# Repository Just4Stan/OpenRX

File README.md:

# OpenRX

Open-source ExpressLRS receiver family — four active boards:

- `OpenRX-Lite`: compact 2.4 GHz SX1281 receiver with ceramic antenna
- `OpenRX-Lite-UFL`: same as Lite with U.FL antenna connector
- `OpenRX-Mono`: single-LR1121 multi-band receiver with 1x U.FL
- `OpenRX-Gemini`: dual-LR1121 Gemini/Xrossband receiver with 2x U.FL

| Model | Band | RF | Front-End | Antenna | ELRS Target |
|-------|------|-----|-----------|---------|-------------|
| **Lite** | 2.4 GHz | SX1281 | 2450FM07D0034 BPF | Ceramic | `Unified_ESP32C3_2400_RX` |
| **Lite UFL** | 2.4 GHz | SX1281 | 2450FM07D0034 BPF | U.FL | `Unified_ESP32C3_2400_RX` |
| **Mono** | Multi-band | LR1121 | RFX2401C + SKY13414 + Johanson IPD | 1x U.FL | `Unified_ESP32C3_LR1121_RX` |
| **Gemini** | Xrossband | 2x LR1121 | 2x (RFX2401C + SKY13414 + Johanson IPD) | 2x U.FL | `Unified_ESP32C3_LR1121_RX` |

Mono and Gemini use the same firmware binary — `radio_nss_2` in hardware.json activates dual-radio mode.

## Active Schematics

- `OpenRX-Lite/esp32c3_sx1281_lite.kicad_sch`
- `OpenRX-Lite-UFL/esp32c3_sx1281_lite.kicad_sch`
- `OpenRX-Mono/esp32c3_lr1121_mono.kicad_sch`
- `OpenRX-Gemini/esp32c3_lr1121_gemini.kicad_sch`

## Documentation

- `OpenRX-Lite/DESIGN.md`
- `OpenRX-Lite-UFL/DESIGN.md`
- `OpenRX-Mono/DESIGN.md`
- `OpenRX-Gemini/DESIGN.md`

## Flashing

All boards expose `5V`, `GND`, `RX`, `TX` pads and a `BOOT` pad (GPIO9 to GND) for initial UART flashing. Mono and Gemini also have a tactile button on GPIO9. After first flash, use Wi-Fi OTA or Betaflight passthrough.

## ELRS Firmware Targets

Hardware JSON files are in `/shared/elrs-targets/`:

- `OpenRX Lite 2400.json`
- `OpenRX Mono LR1121.json`
- `OpenRX Gemini LR1121.json`
- `targets_entries.json`

## KiCad Libraries

All projects use KiCad 9 with project-local libraries only — no global library dependencies.

`shared/libs/` contains:

| Library | Contents |
|---------|----------|
| `OpenRX-Shared.kicad_sym` | Symbols: ESP32-C3, LR1121, SX1281, RFX2401C, SKY13414, TLV75533, Johanson IPD, 2450FM07D0034, antennas, LED, connectors |
| `OpenRX-Shared.pretty` | Footprints: QFN-14/16/24/32, X2SON, antenna, filter, LED, switch, solder pads |
| `OpenRX-Shared.3dshapes` | 3D models (.step + .wrl) |

All symbols include an `LCSC Part` property for JLCPCB BOM export.

## Datasheets

Shared local cache in `datasheets/common/`. All active IC/RF datasheets are present locally.

## Sourcing

Current low-stock / JLCPCB Global Sourcing candidates:

- `C255353` SKY13414-485LF
- `C19842466` 0900PC16J0042001E (consign from DigiKey)
- `C7498014` LR1121IMLTRT
- `C2151551` SX1281IMLTRT (for 1000 pcs Lite build)
- `C2651081` 2450FM07D0034

## License

**CERN Open Hardware Licence Version 2 - Strongly Reciprocal** ([CERN-OHL-S-2.0](https://ohwr.org/cern_ohl_s_v2.txt)). See [LICENSE](LICENSE).

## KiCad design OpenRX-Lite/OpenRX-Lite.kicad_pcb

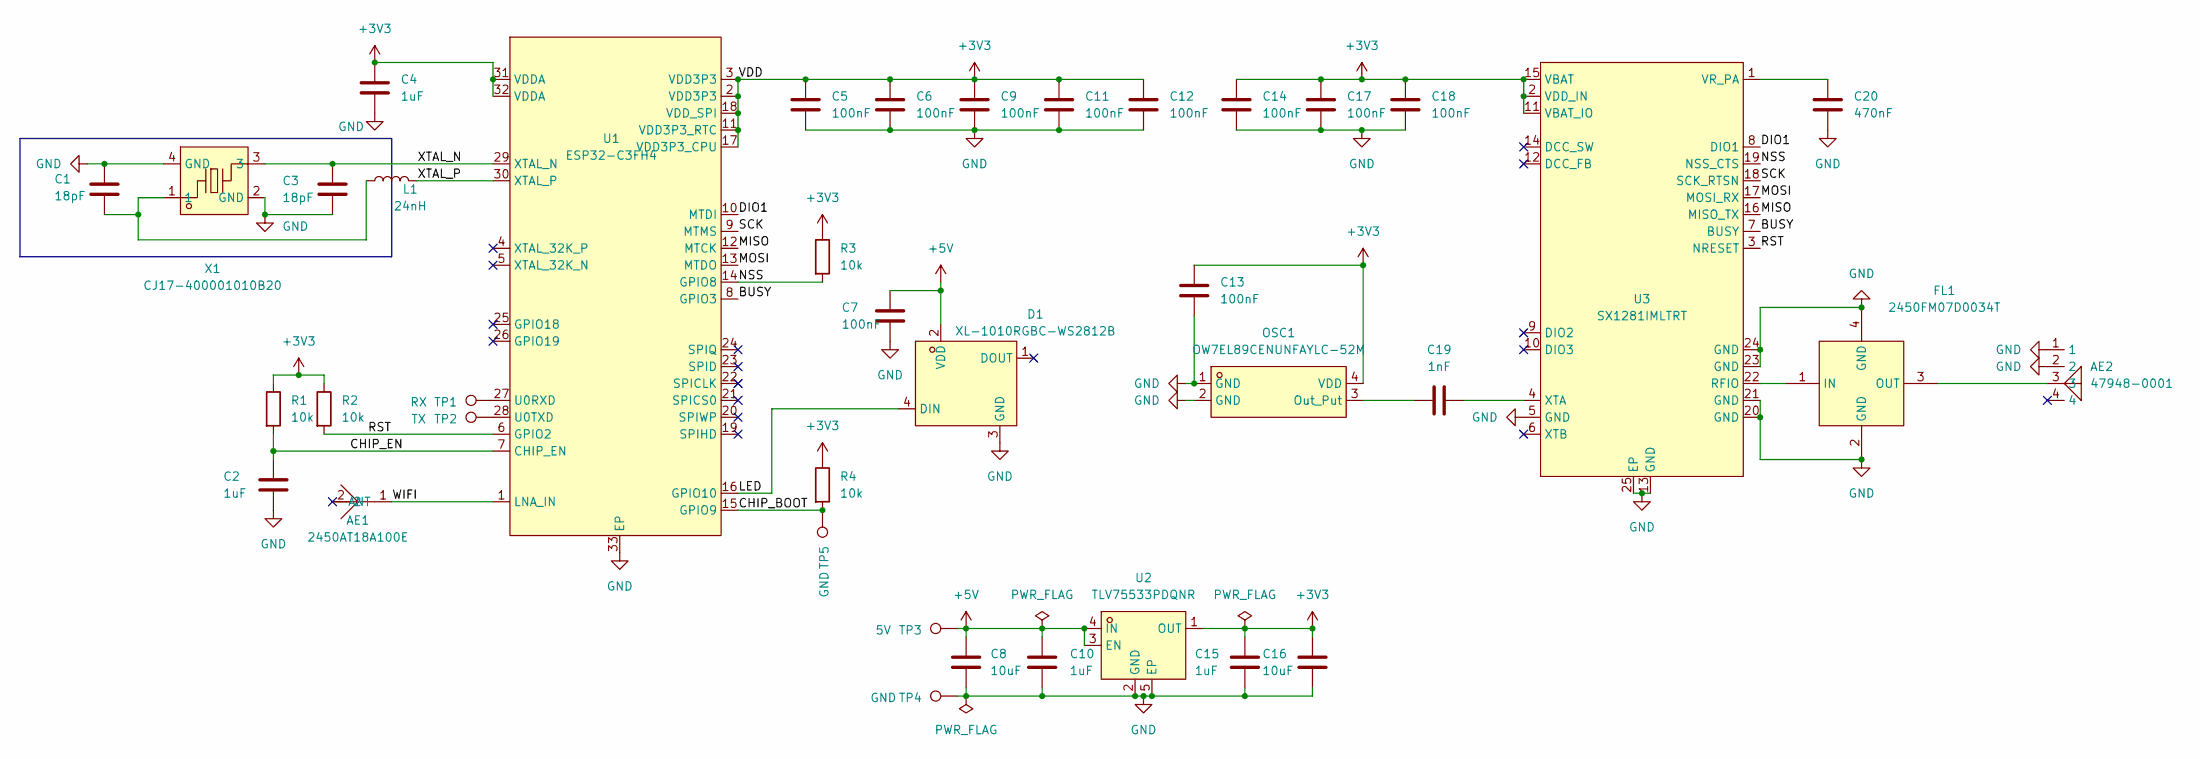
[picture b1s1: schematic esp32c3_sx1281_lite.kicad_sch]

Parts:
AE1: 2450AT18A100E; ANT-SMD_L3.2-W1.6; LCSC Part C89334
AE2: 47948-0001; ANT-SMD_47948-0001; LCSC Part C152351
C1, C3: 18pF; C_0201_0603Metric; LCSC C62164
C2, C4, C10, C15: 1uF; C_0201_0603Metric; LCSC C76935
C5, C6, C7, C9, C11, C12, C13, C14, C17, C18: 100nF; C_0201_0603Metric; LCSC C76939
C8, C16: 10uF; C_0402_1005Metric; LCSC C15525
C19: 1nF; C_0201_0603Metric; LCSC C66942
C20: 470nF; C_0201_0603Metric; LCSC C85926
D1: XL-1010RGBC-WS2812B; LED-SMD_4P-L1.0-W1.0-TL_XL-1010RGBC-WS2812B; LCSC Part C5349953
FL1: 2450FM07D0034T; FILTER-SMD_4P-L1.0-W0.5-L; MPN 2450FM07D0034T; LCSC Part C2651081
L1: 24nH; L_0201_0603Metric; LCSC C206441
OSC1: OW7EL89CENUNFAYLC-52M; OSC-SMD_4P-L2.0-W1.6-BL_TXC_7Z; LCSC Part C22434896
R1, R2, R3, R4: 10k; R_0201_0603Metric; LCSC C106225
TP1: RX; SolderPad_1.2x2.0mm
TP2: TX; SolderPad_1.2x2.0mm
TP3: 5V; SolderPad_1.2x2.0mm
TP4, TP5: GND; SolderPad_1.2x2.0mm
U1: ESP32-C3FH4; QFN-32_L5.0-W5.0-P0.50-TL-EP3.7; LCSC Part C2858491
U2: TLV75533PDQNR; X2SON-4_L1.0-W1.0-P0.65-TL-EP; LCSC Part C2861882
U3: SX1281IMLTRT; QFN-24_L4.0-W4.0-P0.50-TL-EP2.6; LCSC Part C2151551
X1: CJ17-400001010B20; CRYSTAL-SMD_4P-L1.6-W1.2-BL; LCSC Part C2875272

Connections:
+3V3: C4.1, C5.1, C6.1, C9.1, C11.1, C12.1, C13.1, C14.1, C15.1, C16.1, C17.1, C18.1, OSC1.4 (VDD), R1.1, R2.1, R3.1, R4.1, U1.2 (VDD3P3), U1.3 (VDD3P3), U1.11 (VDD3P3_RTC), U1.17 (VDD3P3_CPU), U1.18 (VDD_SPI), U1.31 (VDDA), U1.32 (VDDA), U2.1 (OUT), U3.2 (VDD_IN), U3.11 (VBAT_IO), U3.15 (VBAT)
+5V: C7.1, C8.1, C10.1, D1.2 (VDD), TP3.1 (1_1), U2.3 (EN), U2.4 (IN)
/ESP32-C3 + SX1281 Core/BUSY: U1.8 (GPIO3), U3.7 (BUSY)
/ESP32-C3 + SX1281 Core/CHIP_BOOT: R4.2, TP5.1 (1_1), U1.15 (GPIO9)
/ESP32-C3 + SX1281 Core/CHIP_EN: C2.1, R1.2, U1.7 (CHIP_EN)
/ESP32-C3 + SX1281 Core/DIO1: U1.10 (MTDI), U3.8 (DIO1)
/ESP32-C3 + SX1281 Core/LED: D1.4 (DIN), U1.16 (GPIO10)
/ESP32-C3 + SX1281 Core/MISO: U1.12 (MTCK), U3.16 (MISO_TX)
/ESP32-C3 + SX1281 Core/MOSI: U1.13 (MTDO), U3.17 (MOSI_RX)
/ESP32-C3 + SX1281 Core/NSS: R3.2, U1.14 (GPIO8), U3.19 (NSS_CTS)
/ESP32-C3 + SX1281 Core/RST: R2.2, U1.6 (GPIO2), U3.3 (NRESET)
/ESP32-C3 + SX1281 Core/SCK: U1.9 (MTMS), U3.18 (SCK_RTSN)
/ESP32-C3 + SX1281 Core/WIFI: AE1.1 (ANT_1), U1.1 (LNA_IN)
/ESP32-C3 + SX1281 Core/XTAL_N: C3.1, U1.29 (XTAL_N), X1.3
/ESP32-C3 + SX1281 Core/XTAL_P: L1.2, U1.30 (XTAL_P)
GND: AE2.1, AE2.2, C1.2, C2.2, C3.2, C4.2, C5.2, C6.2, C7.2, C8.2, C9.2, C10.2, C11.2, C12.2, C13.2, C14.2, C15.2, C16.2, C17.2, C18.2, C20.2, D1.3 (GND), FL1.2 (GND), FL1.4 (GND), OSC1.1 (GND), OSC1.2 (GND), TP4.1 (1_1), U1.33 (EP), U2.2 (GND), U2.5 (EP), U3.5 (GND), U3.13 (GND), U3.20 (GND), U3.21 (GND), U3.23 (GND), U3.24 (GND), U3.25 (EP), X1.2 (GND), X1.4 (GND)
unnamed: C1.1, L1.1, X1.1
unnamed: FL1.1 (IN), U3.22 (RFIO)
unnamed: AE2.3, FL1.3 (OUT)
unnamed: C19.1, OSC1.3 (Out_Put)
unnamed: TP1.1 (1_1), U1.27 (U0RXD)
unnamed: TP2.1 (1_1), U1.28 (U0TXD)
unnamed: C20.1, U3.1 (VR_PA)
unnamed: C19.2, U3.4 (XTA)

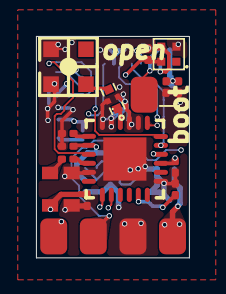
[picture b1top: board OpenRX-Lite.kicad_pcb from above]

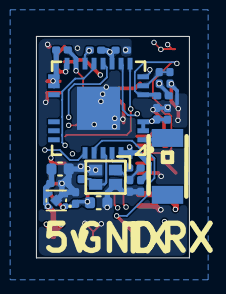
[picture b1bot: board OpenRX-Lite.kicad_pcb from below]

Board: 6 copper layers, 8.5 x 12.3 mm, 39 parts (20 on the bottom side), 24 nets.

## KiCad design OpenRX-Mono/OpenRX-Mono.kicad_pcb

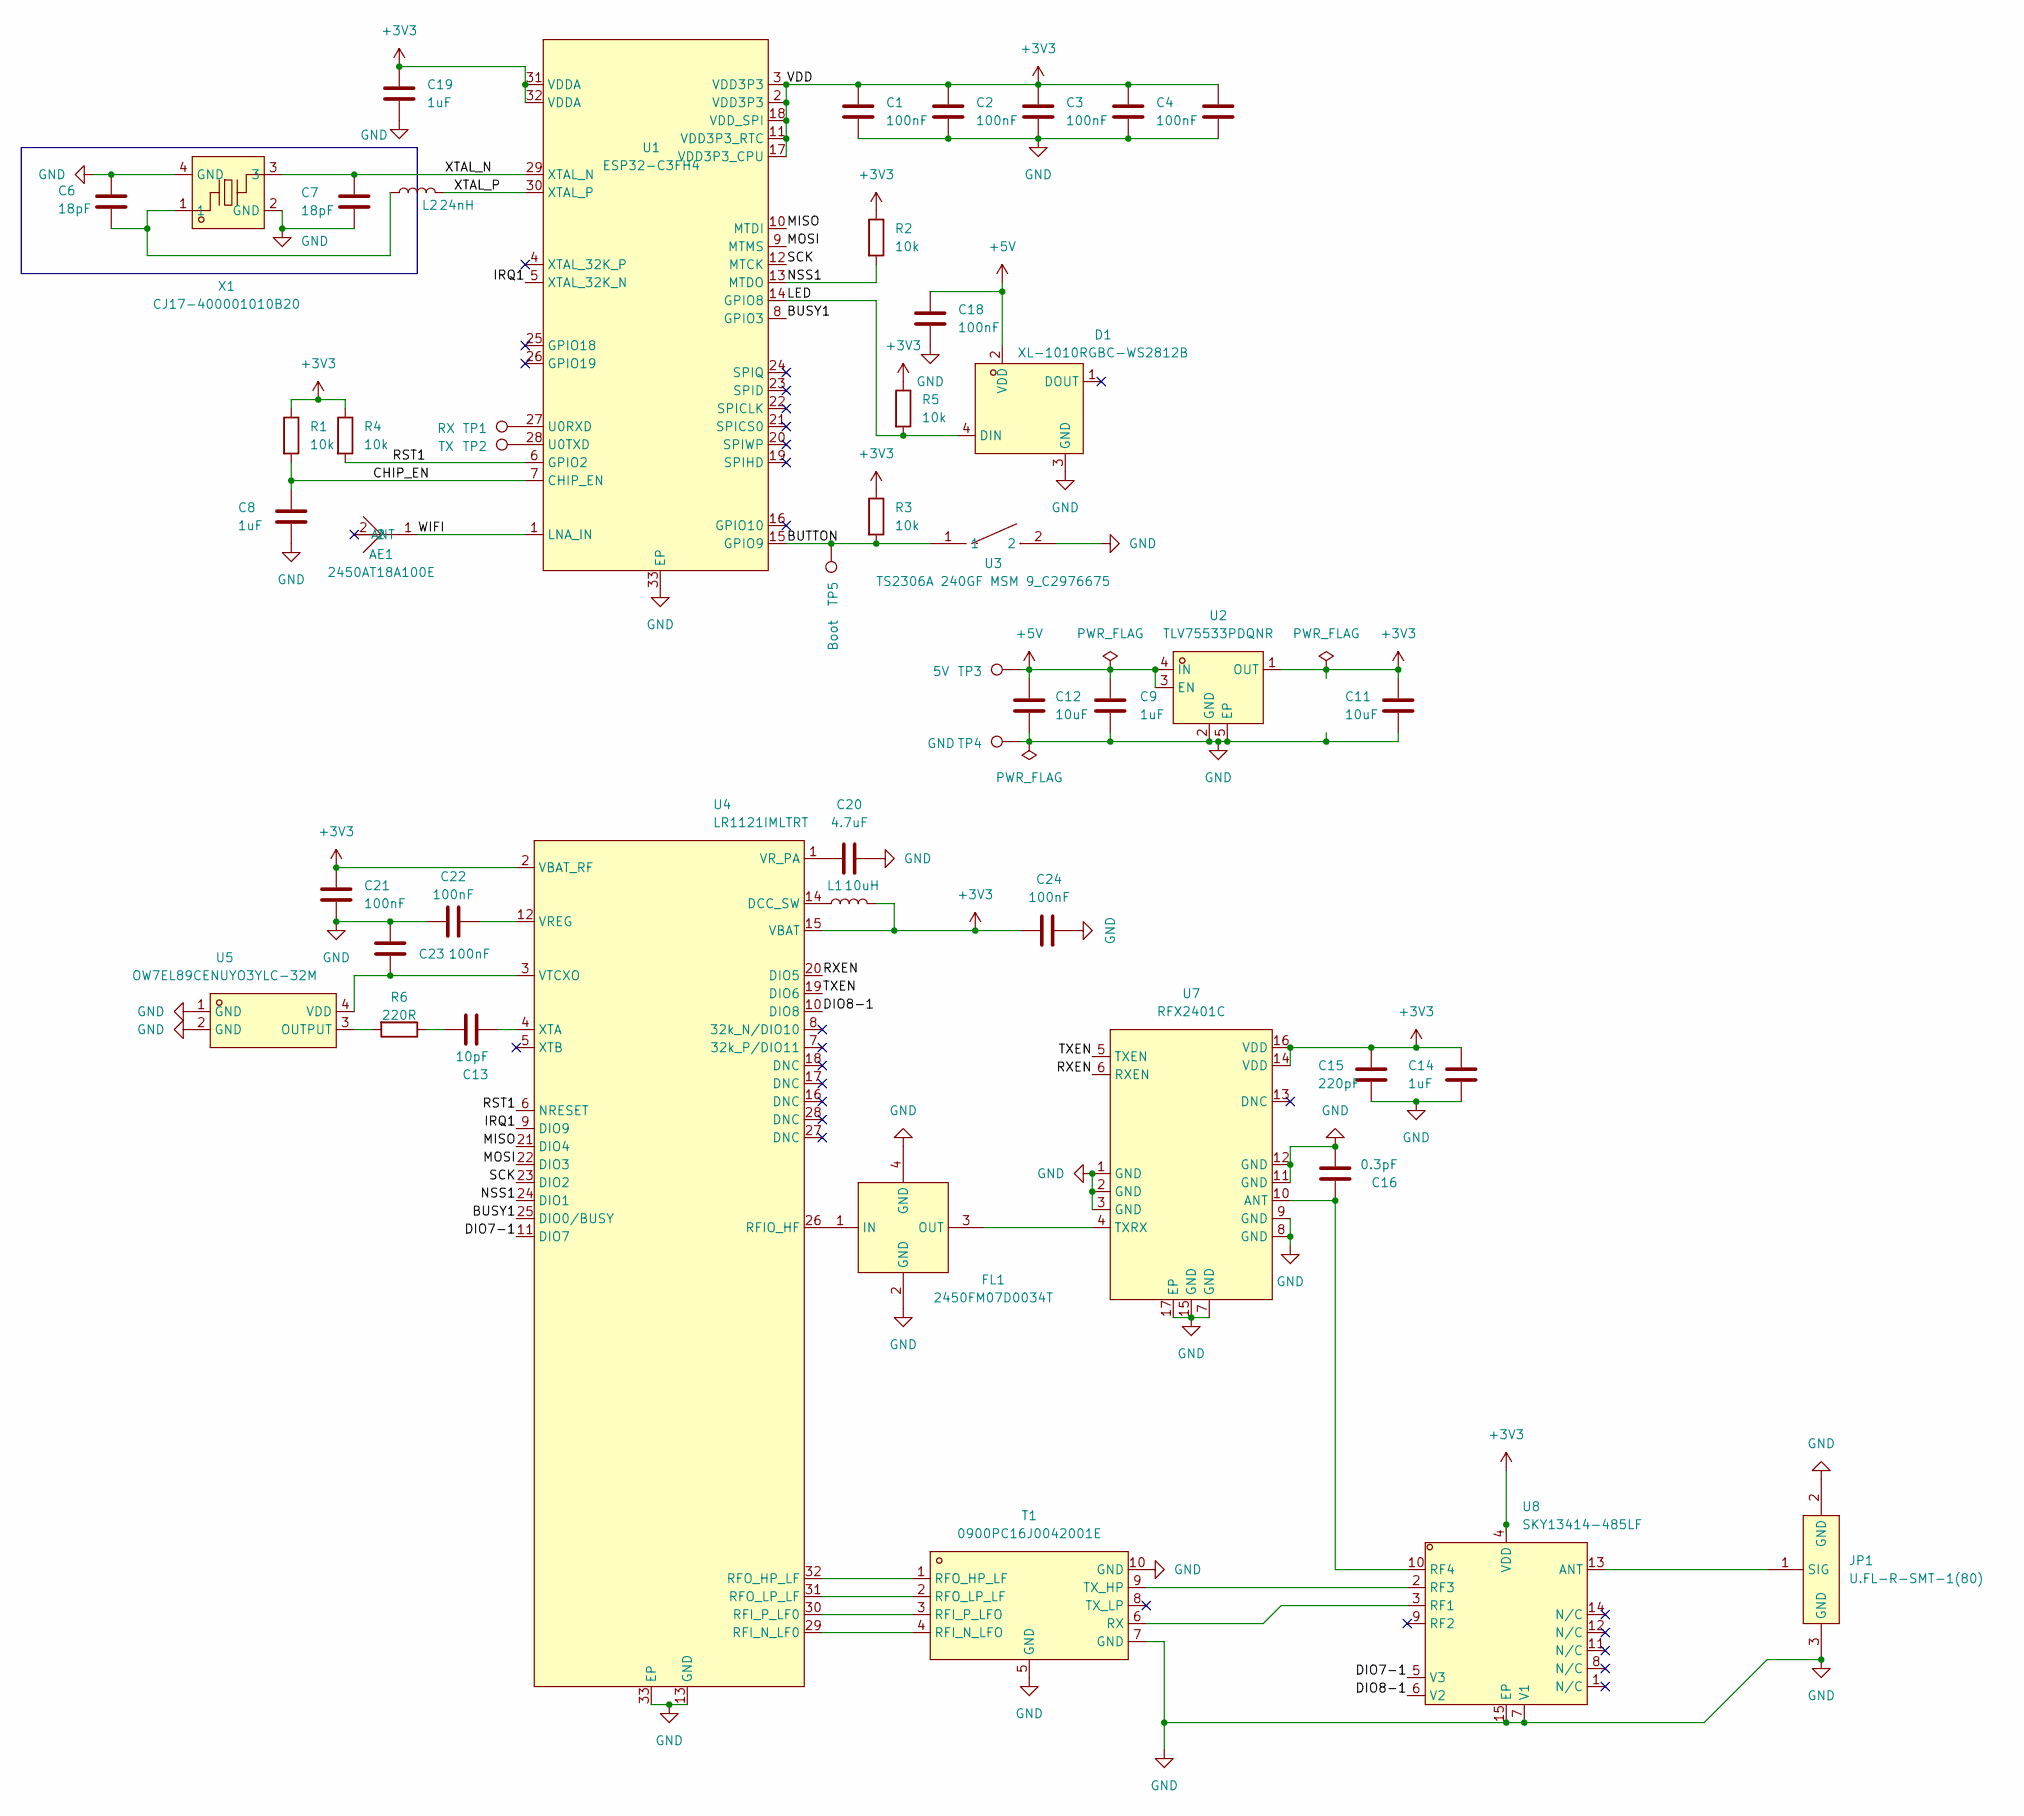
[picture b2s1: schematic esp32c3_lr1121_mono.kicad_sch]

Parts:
AE1: 2450AT18A100E; ANT-SMD_L3.2-W1.6; LCSC Part C89334
C1, C2, C3, C4, C5, C18, C21, C22, C23, C24: 100nF; C_0201_0603Metric; LCSC C76939
C6, C7: 18pF; C_0201_0603Metric; LCSC C62164
C8, C9, C14, C19: 1uF; C_0201_0603Metric; LCSC C76935
C11, C12: 10uF; C_0402_1005Metric; LCSC C15525
C13: 10pF; C_0201_0603Metric; LCSC C76921
C15: 220pF; C_0201_0603Metric; LCSC C62548
C16: 0.3pF; C_0201_0603Metric; LCSC C76927
C20: 4.7uF; C_0402_1005Metric; LCSC C23733
D1: XL-1010RGBC-WS2812B; LED-SMD_4P-L1.0-W1.0-TL_XL-1010RGBC-WS2812B; LCSC Part C5349953
FL1: 2450FM07D0034T; FILTER-SMD_4P-L1.0-W0.5-L; MPN 2450FM07D0034T; LCSC Part C2651081
JP1: U.FL-R-SMT-1(80); RF-SMD_FRF05002-JSS103M; LCSC Part C88374
L1: 10uH; L_0603_1608Metric; LCSC C1035
L2: 24nH; L_0201_0603Metric; LCSC C206441
R1, R2, R3, R4, R5: 10k; R_0201_0603Metric; LCSC C106225
R6: 220R; R_0201_0603Metric; LCSC C274342
T1: 0900PC16J0042001E; FILTER-SMD_10P-L2.0-W1.6-BL; LCSC Part C19842466
TP1: RX; SolderPad_1.2x2.0mm
TP2: TX; SolderPad_1.2x2.0mm
TP3: 5V; SolderPad_1.2x2.0mm
TP4: GND; SolderPad_1.2x2.0mm
TP5: Boot; SolderPad_1.2x2.0mm
U1: ESP32-C3FH4; QFN-32_L5.0-W5.0-P0.50-TL-EP3.7; LCSC Part C2858491
U2: TLV75533PDQNR; X2SON-4_L1.0-W1.0-P0.65-TL-EP; LCSC Part C2861882
U3: TS2306A 240GF MSM 9_C2976675; SW-SMD_4P-L3.0-W2.0-P0.85-LS3.5; LCSC Part C2976675
U4: LR1121IMLTRT; QFN-32_L5.0-W5.0-P0.50-BL-EP3.7; LCSC Part C7498014
U5: OW7EL89CENUYO3YLC-32M; OSC-SMD_4P-L2.0-W1.6-BL_TXC_7Z; LCSC Part C22381772
U7: RFX2401C; QFN-16_L3.0-W3.0-P0.50-BL-EP1.7; LCSC Part C19213
U8: SKY13414-485LF; QFN-14_L2.0-W2.0-P0.45-BL-EP; MPN SKY13414-485LF; LCSC Part C255353
X1: CJ17-400001010B20; CRYSTAL-SMD_4P-L1.6-W1.2-BL; LCSC Part C2875272

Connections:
+3V3: C1.1, C2.1, C3.1, C4.1, C5.1, C11.1, C14.1, C15.1, C19.1, C21.1, C24.2, L1.2, R1.1, R2.1, R3.1, R4.1, R5.1, U1.2 (VDD3P3), U1.3 (VDD3P3), U1.11 (VDD3P3_RTC), U1.17 (VDD3P3_CPU), U1.18 (VDD_SPI), U1.31 (VDDA), U1.32 (VDDA), U2.1 (OUT), U4.2 (VBAT_RF), U4.15 (VBAT), U7.14 (VDD), U7.16 (VDD), U8.4 (VDD)
+5V: C9.1, C12.1, C18.1, D1.2 (VDD), TP3.1 (1_1), U2.3 (EN), U2.4 (IN)
/ESP32-C3 + LR1121 Mono/BUSY1: U1.8 (GPIO3), U4.25 (DIO0/BUSY)
/ESP32-C3 + LR1121 Mono/BUTTON: R3.2, TP5.1 (1_1), U1.15 (GPIO9), U3.1
/ESP32-C3 + LR1121 Mono/CHIP_EN: C8.1, R1.2, U1.7 (CHIP_EN)
/ESP32-C3 + LR1121 Mono/DIO7-1: U4.11 (DIO7), U8.5 (V3)
/ESP32-C3 + LR1121 Mono/DIO8-1: U4.10 (DIO8), U8.6 (V2)
/ESP32-C3 + LR1121 Mono/IRQ1: U1.5 (XTAL_32K_N), U4.9 (DIO9)
/ESP32-C3 + LR1121 Mono/LED: D1.4 (DIN), R5.2, U1.14 (GPIO8)
/ESP32-C3 + LR1121 Mono/MISO: U1.10 (MTDI), U4.21 (DIO4)
/ESP32-C3 + LR1121 Mono/MOSI: U1.9 (MTMS), U4.22 (DIO3)
/ESP32-C3 + LR1121 Mono/NSS1: R2.2, U1.13 (MTDO), U4.24 (DIO1)
/ESP32-C3 + LR1121 Mono/RST1: R4.2, U1.6 (GPIO2), U4.6 (NRESET)
/ESP32-C3 + LR1121 Mono/RXEN: U4.20 (DIO5), U7.6 (RXEN)
/ESP32-C3 + LR1121 Mono/SCK: U1.12 (MTCK), U4.23 (DIO2)
/ESP32-C3 + LR1121 Mono/TXEN: U4.19 (DIO6), U7.5 (TXEN)
/ESP32-C3 + LR1121 Mono/WIFI: AE1.1 (ANT_1), U1.1 (LNA_IN)
/ESP32-C3 + LR1121 Mono/XTAL_N: C7.1, U1.29 (XTAL_N), X1.3
/ESP32-C3 + LR1121 Mono/XTAL_P: L2.2, U1.30 (XTAL_P)
GND: C1.2, C2.2, C3.2, C4.2, C5.2, C6.2, C7.2, C8.2, C9.2, C11.2, C12.2, C14.2, C15.2, C16.2, C18.2, C19.2, C20.2, C21.2, C22.1, C23.1, C24.1, D1.3 (GND), FL1.2 (GND), FL1.4 (GND), JP1.2 (GND), JP1.3 (GND), T1.5 (GND), T1.7 (GND), T1.10 (GND), TP4.1 (1_1), U1.33 (EP), U2.2 (GND), U2.5 (EP), U3.2, U4.13 (GND), U4.33 (EP), U5.1 (GND), U5.2 (GND), U7.1 (GND), U7.2 (GND), U7.3 (GND), U7.7 (GND), U7.8 (GND), U7.9 (GND), U7.11 (GND), U7.12 (GND), U7.15 (GND), U7.17 (EP), U8.7 (V1), U8.15 (EP), X1.2 (GND), X1.4 (GND)
unnamed: C6.1, L2.1, X1.1
unnamed: C13.1, R6.1
unnamed: FL1.1 (IN), U4.26 (RFIO_HF)
unnamed: FL1.3 (OUT), U7.4 (TXRX)
unnamed: JP1.1 (SIG), U8.13 (ANT)
unnamed: T1.4 (RFI_N_LFO), U4.29 (RFI_N_LF0)
unnamed: T1.3 (RFI_P_LFO), U4.30 (RFI_P_LF0)
unnamed: T1.1 (RFO_HP_LF), U4.32 (RFO_HP_LF)
unnamed: T1.2 (RFO_LP_LF), U4.31 (RFO_LP_LF)
unnamed: T1.6 (RX), U8.3 (RF1)
unnamed: T1.9 (TX_HP), U8.2 (RF3)
unnamed: TP1.1 (1_1), U1.27 (U0RXD)
unnamed: TP2.1 (1_1), U1.28 (U0TXD)
unnamed: L1.1, U4.14 (DCC_SW)
unnamed: C22.2, U4.12 (VREG)
unnamed: C20.1, U4.1 (VR_PA)
unnamed: C23.2, U4.3 (VTCXO), U5.4 (VDD)
unnamed: C13.2, U4.4 (XTA)
unnamed: R6.2, U5.3 (OUTPUT)
unnamed: C16.1, U7.10 (ANT), U8.10 (RF4)

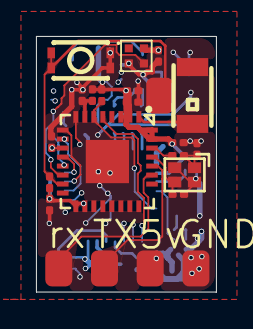
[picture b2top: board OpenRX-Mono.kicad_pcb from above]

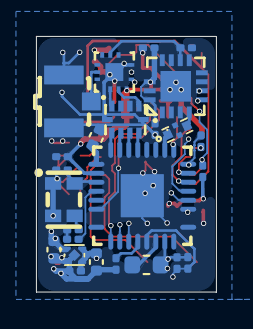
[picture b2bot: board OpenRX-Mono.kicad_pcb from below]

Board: 6 copper layers, 10.0 x 14.2 mm, 48 parts (25 on the bottom side), 40 nets.

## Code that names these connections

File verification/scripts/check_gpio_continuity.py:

#!/usr/bin/env python3
"""
Verify schematic ↔ hardware.json continuity for each OpenRX board.

Source of truth: kicad-cli-exported netlist.xml next to each schematic.
Strategy:
  - Build ESP32-C3 pin-function → GPIO number table from the datasheet.
  - For the ESP32 component in the netlist, map each pinfunction to a GPIO.
  - Compare the GPIO numbers against the ELRS target JSON's declared pins.

Run after regenerating netlists:
  for d in OpenRX-Lite OpenRX-Lite-UFL OpenRX-Mono OpenRX-Gemini; do
    kicad-cli sch export netlist --format kicadxml \
        -o $d/netlist.xml $d/*core*.kicad_sch $d/esp32c3*.kicad_sch 2>/dev/null
  done
"""
from __future__ import annotations

import json
import os
import re
import sys
import xml.etree.ElementTree as ET

BASE = os.path.dirname(os.path.dirname(os.path.dirname(os.path.abspath(__file__))))
ELRS = os.path.join(BASE, "shared", "elrs-targets")

# ── ESP32-C3 (QFN32) pinfunction → GPIO# ───────────────────────────────
# Taken from the ESP32-C3 datasheet Table 3-2.
ESP32C3_PIN_TO_GPIO: dict[str, int] = {
    "XTAL_32K_P":  0,
    "XTAL_32K_N":  1,
    "GPIO2":       2,
    "GPIO3":       3,
    "MTMS":        4,
    "MTDI":        5,
    "MTCK":        6,
    "MTDO":        7,
    "GPIO8":       8,
    "GPIO9":       9,
    "GPIO10":      10,
    "VDD_SPI":     11,
    "SPIHD":       12,
    "SPIWP":       13,
    "SPICS0":      14,
    "SPICLK":      15,
    "SPID":        16,
    "SPIQ":        17,
    "GPIO18":      18,
    "GPIO19":      19,
    "U0RXD":       20,
    "U0TXD":       21,
}

# Net-name in schematic → ELRS JSON field. Uses a regex so the schematics
# are free to number signals per-radio (BUSY1, BUSY2, etc.) and we still
# find them.
NET_TO_FIELD_COMMON: list[tuple[re.Pattern[str], str]] = [
    (re.compile(r"^RX$"),           "serial_rx"),
    (re.compile(r"^TX$"),           "serial_tx"),
    (re.compile(r"^MOSI$"),         "radio_mosi"),
    (re.compile(r"^MISO$"),         "radio_miso"),
    (re.compile(r"^SCK$"),          "radio_sck"),
    (re.compile(r"^BUSY1?$"),       "radio_busy"),
    (re.compile(r"^IRQ1?$"),        "radio_dio1"),
    (re.compile(r"^NSS1?$"),        "radio_nss"),
    (re.compile(r"^RST1?$"),        "radio_rst"),
    (re.compile(r"^LED$"),          "led"),
    (re.compile(r"^LED$"),          "led_rgb"),  # Gemini uses RGB LED
    (re.compile(r"^BUTTON$|^BTN$"), "button"),
]

NET_TO_FIELD_RADIO_B: list[tuple[re.Pattern[str], str]] = [
    (re.compile(r"^BUSY2$"), "radio_busy_2"),
    (re.compile(r"^IRQ2$"),  "radio_dio1_2"),
    (re.compile(r"^NSS2$"),  "radio_nss_2"),
    (re.compile(r"^RST2$"),  "radio_rst_2"),
]


def parse_pinfunction(pinfunc: str) -> int | None:
    """Accept either 'GPIO3' or 'GPIO3_8' (<name>_<pin>) or 'MTDI_10'."""
    if not pinfunc:
        return None
    base = pinfunc.split("_")[0]
    # Some library variants expand: 'GPIO3' pin is GPIO3 directly
    if base in ESP32C3_PIN_TO_GPIO:
        return ESP32C3_PIN_TO_GPIO[base]
    # Handle 'XTAL_32K_P_4' style where base split was too aggressive
    m = re.match(r"(XTAL_32K_[PN])", pinfunc)
    if m:
        return ESP32C3_PIN_TO_GPIO[m.group(1)]
    return None


def gather_esp32_nets(netlist_xml: str) -> tuple[str, dict[str, int]]:
    """Return (esp_ref, {net_name_stripped: gpio#}) for the ESP32 on this netlist."""
    tree = ET.parse(netlist_xml)
    root = tree.getroot()

    esp_ref = None
    for comp in root.iter("comp"):
        if "ESP32" in comp.findtext("value", ""):
            esp_ref = comp.get("ref")
            break
    if not esp_ref:
        return "", {}

    out: dict[str, int] = {}
    for net in root.iter("net"):
        raw = net.get("name", "")
        name = raw.strip("/").split("/")[-1].upper()
        for node in net.iter("node"):
            if node.get("ref") != esp_ref:
                continue
            pinfunc = node.get("pinfunction") or ""
            gpio = parse_pinfunction(pinfunc)
            if gpio is not None:
                # Only record the first assignment for a given net (they
                # should all agree since a net→ESP32 is usually 1 pin).
                out.setdefault(name, gpio)
    return esp_ref, out


def check_board(name: str, netlist: str, json_name: str, dual_radio: bool) -> int:
    print(f"\n── {name} ──")
    if not os.path.exists(netlist):
        print(f"  ERROR: netlist missing: {netlist}"); return 1
    json_path = os.path.join(ELRS, json_name)
    if not os.path.exists(json_path):
        print(f"  ERROR: json missing: {json_path}"); return 1

    esp_ref, pins = gather_esp32_nets(netlist)
    if not pins:
        print(f"  ERROR: no ESP32 pins resolved"); return 1

    with open(json_path) as f:
        conf = json.load(f)

    rules = list(NET_TO_FIELD_COMMON)
    if dual_radio:
        rules += NET_TO_FIELD_RADIO_B

    errors = 0
    seen_fields: set[str] = set()
    for net_name, gpio in sorted(pins.items()):
        matched = False
        for rx, field in rules:
            if not rx.match(net_name):
                continue
            if field not in conf:
                continue
            want = conf[field]
            seen_fields.add(field)
            if gpio == want:
                print(f"  OK    {field:16s} net={net_name:9s} GPIO{gpio}")
            else:
                print(f"  FAIL  {field:16s} net={net_name:9s} schematic=GPIO{gpio}  json={want}")
                errors += 1
            matched = True
            break
        if not matched:
            # Not tied to a JSON field — still print for visibility
            pass

    # Any configured JSON pins for which we saw no matching net?
    expected_fields = {f for _, f in rules if f in conf}
    missing = expected_fields - seen_fields
    for m in sorted(missing):
        # led_rgb and led are aliases — tolerate one missing if the other was seen
        if m == "led_rgb" and "led" in seen_fields:
            continue
        if m == "led" and "led_rgb" in seen_fields:
            continue
        print(f"  MISS  {m:16s} expected GPIO{conf[m]} — no net mapped")
        errors += 1

    print(f"  ESP32 ref: {esp_ref}, nets resolved: {len(pins)}, errors: {errors}")
    return errors


def main() -> int:
    rc = 0
    rc += check_board(
        "OpenRX-Lite",
        os.path.join(BASE, "OpenRX-Lite", "netlist.xml"),
        "OpenRX Lite 2400.json",
        dual_radio=False,
    )
    rc += check_board(
        "OpenRX-Lite-UFL",
        os.path.join(BASE, "OpenRX-Lite-UFL", "netlist.xml"),
        "OpenRX Lite 2400.json",
        dual_radio=False,
    )
    rc += check_board(
        "OpenRX-Mono",
        os.path.join(BASE, "OpenRX-Mono", "netlist.xml"),
        "OpenRX Mono LR1121.json",
        dual_radio=False,
    )
    rc += check_board(
        "OpenRX-Gemini",
        os.path.join(BASE, "OpenRX-Gemini", "netlist.xml"),
        "OpenRX Gemini LR1121.json",
        dual_radio=True,
    )
    print(f"\nTotal errors: {rc}")
    return 0 if rc == 0 else 1


if __name__ == "__main__":
    sys.exit(main())

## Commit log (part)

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2026-03-23 Initial repo: 6-receiver product lineup, core BOM, shared datasheets
    OpenRX is an open-source ExpressLRS 4.0 receiver family covering
    budget nano to Xrossband Gemini. All designs use ESP32-C3 MCU with
    SX1281 (2.4GHz) or LR1121 (dual-band) RF transceivers.
    CERN-OHL-S v2 licensed. Part of the OpenDrone ecosystem.
2026-03-23 Add OpenRX-Lite: budget 2.4GHz receiver (ESP32-C3 + SX1281)
    Smallest/cheapest receiver. No PA/LNA, ceramic antenna, 16x12mm.
    Includes SCHEMATIC.md, BOM.md, imported LCSC libs, datasheets.
    KiCad schematic/PCB are starter shells awaiting capture.
2026-03-23 Add OpenRX-Nano: standard 2.4GHz with RFX2401C PA+LNA
    Mid-range all-rounder. ESP32-C3 + SX1281 + RFX2401C, UFL, 20x13mm.
    First receiver aligned to RFX2401C front-end standard.
2026-03-23 Add OpenRX-Dual: dual-band switchable receiver (ESP32-C3 + LR1121)
    Single LR1121 with both sub-GHz and 2.4GHz RF paths.
    Still uses SE2431L in docs, pending RFX2401C migration.
2026-03-23 Add OpenRX-900: budget sub-GHz receiver (ESP32-C3 + LR1121)
    Budget long-range receiver using LR1121 in sub-GHz only mode.
    LR1121 pinout needs reconciliation before schematic capture.
2026-03-23 Add OpenRX-PWM: 6ch PWM receiver for fixed wing (ESP32-C3 + SX1281)
    PWM outputs for servos/ESCs. GPIO allocation documented with
    4ch (safe) and 6ch (DIO2 switching) options.
    Still uses SE2431L in docs, pending RFX2401C migration.
2026-03-23 Add OpenRX-Gemini: flagship Xrossband receiver (ESP32-C3 + 2x LR1121)
    Simultaneous 2.4GHz + 900MHz Gemini mode. Dual LR1121 on shared
    SPI bus. Tightest GPIO allocation of the family.
    Still uses SE2431L on 2.4GHz path, pending RFX2401C migration.
2026-03-23 Consolidate docs: 1 README + KICAD_WORKFLOW + 1 DESIGN.md per receiver
    - Merge SCHEMATIC.md + BOM.md into single DESIGN.md per receiver
    - Delete OPENRX_ELRS_4_RECEIVER_PORTFOLIO.md (content integrated)
    - Delete REPO_AUDIT_2026-03-23.md (issues addressed)
    - Fold CORE_BOM into README.md architecture table
    - Rename KICAD_WORKFLOW_AND_ELRS_COMPATIBILITY.md to KICAD_WORKFLOW.md
    - Rewrite KICAD_WORKFLOW with step-by-step capture instructions
2026-03-23 Remove leftover SCHEMATIC.md and BOM.md files (content in DESIGN.md)
2026-03-23 Fix RF path: DEA102700LT-6307A2 only, no discrete matching
    RadioMaster uses only the DEA LPF between SX1281 and antenna/FEM
    on all their receivers. Remove stale L-match and pi-filter references.
    Add mandatory 0.3pF 5th harmonic cap on RFX2401C ANT output.
2026-03-23 Fix all DESIGN.md: RFX2401C, DEA LPF, LR1121 pinout, FEM control
    - Lite: remove L-match network, use DEA102700LT-6307A2 only
    - Nano: clarify DEA LPF path, mark 0.3pF as mandatory, SE2431L as EOL
    - 900: fix LR1121 RFSW description, confirm 4x4mm package
    - Dual: SE2431L→RFX2401C, FEM via LR1121 RFSW not MCU GPIO, BOM $9→$7.62
    - PWM: SE2431L→RFX2401C, DEA LPF + 0.3pF path, BOM $7.40→$6.02
    - Gemini: SE2431L→RFX2401C, fix FEM control model, BOM $10.84→$9.46
2026-03-23 Update all DESIGN.md: TLV75533 X2SON LDO, XL-1010 1x1mm LED
    - Lite/Nano/900/Dual: ME6211 SOT-23-5 → TLV75533PDQNR X2SON-4 (1x1mm)
    - Gemini: keeps AP2112K (600mA needed for dual radios)
    - PWM: keeps AMS1117 (needs >6V input range)
    - All: WS2812B-2020 → XL-1010RGBC-WS2812B (1x1mm)
    - Updated cap values for TLV755 (1uF local + 10uF bulk)
2026-03-23 Import DEA102700LT-6307A2 LPF into shared library (C574024)
2026-03-23 Import U.FL-R-SMT-1(80) UFL connector into shared library (C88374)
2026-03-23 Import Molex 479480001 tower ceramic antenna (C152351) for ELRS RF
2026-03-23 Add solder pad footprints: 1.0x1.5mm and 1.0x0.8mm compact
2026-03-23 Unify library tables, import RFX2401C, Lite schematic capture
    - All 6 projects now share OpenRX-Shared + OpenRX-Lite lib tables
    - Import RFX2401C (C19213) into shared library with 3D model path fix
    - OpenRX-Lite schematic: 0 ERC errors (captured in KiCad GUI)
    - Add .gitignore for .lck and .history files
2026-03-23 Fix passive footprints to 0402/0603, add LCSC part numbers
    - All caps/resistors: 0201 → 0402 (1005 Metric)
    - 10uF bulk caps: 0402 → 0603 (1608 Metric)
    - Added LCSC field to all 23 passives:
    100nF=C1525, 1uF=C52923, 10uF=C15525, 10pF=C32949,
    470nF=C1543, 1nF=C1523, 10k=C25744
    - All JLCPCB basic parts, zero extended part setup fees on passives
2026-03-23 Switch passives to 0201 with correct LCSC basic parts
    - 100nF: C14858 (0201 X5R 6.3V)
    - 1uF: C77857 (0201 X5R 6.3V)
    - 10pF: C14854 (0201 C0G 25V)
    - 470nF: C304534 (0201 X5R 6.3V)
    - 1nF: C80390 (0201 X7R 25V)
    - 10k: C172043 (0201 1%)
2026-03-23 10uF caps to 0402 (C15525), all other passives stay 0201
2026-03-23 Add LCSC fields to all 24 passives in shared schematic
2026-03-23 Separate Lite and Nano schematics, stop sharing one file
    Sharing one .kicad_sch between projects doesn't work - KiCad
    overwrites instance data when either project saves.
    - Lite: restored pre-Nano schematic as local esp32c3_sx1281_lite.kicad_sch
    - Nano: copied current shared sheet as local esp32c3_sx1281_rx_core.kicad_sch
    - Each project now has its own schematic file
2026-03-23 Lite + Nano schematics: LCSC fields, fix 10uF to 0402, drop 0.3pF cap
    - All passives in both schematics have LCSC fields
    - 10uF caps fixed from 0201 to 0402 (C15525)
    - Nano C22 (0.3pF): removed discrete cap, use trace capacitance instead
    - 0 ERC errors on both schematics
2026-03-23 Import LR1121 (C7498014) and 32MHz TCXO (C22434888) into shared library
2026-03-23 Import Johanson 0900PC16J0042001E LR11xx sub-GHz IPD (C19842466) and LR1121 + 32MHz TCXO
2026-03-23 OpenRX-900: add all LCSC fields, fix 4.7uF to 0402
    - C20 (4.7uF): C23733, footprint fixed from 0201 to 0402
    - R5/R6/R7 (100k): C25741, RFSW pull-downs
    - L1 (10uH): C1035, 0603 DC-DC inductor
    - U4 (LR1121): C7498014
    - U5 (32MHz TCXO): C22434888
    - T1 (Johanson IPD): C19842466
2026-03-23 OpenRX-Dual: set up project, copy 900 schematic as base
    Copy esp32c3_lr1121_900.kicad_sch as starting point.
    Next step: add RFX2401C + DEA LPF + second UFL for 2.4GHz path in KiCad GUI.
    Wire LR1121 RFIO_HF → DEA → RFX2401C, RFSW DIO5/DIO6 → RXEN/TXEN.
2026-03-23 OpenRX-Dual: complete schematic, 0 ERC errors, all LCSC fields
    Dual-band switchable receiver based on 900 schematic plus:
    - RFX2401C (C19213) on 2.4GHz path via DEA LPF
    - LR1121 RFSW DIO5/DIO6 drive RFX2401C RXEN/TXEN
    - Second UFL for 2.4GHz antenna
    - 1uF + 220pF VDD decoupling for RFX2401C
2026-03-23 OpenRX-Gemini: set up project, copy Dual schematic as base
2026-03-23 Add LCSC to 220R resistor (C25092) in Dual TCXO path
    220R series + 10pF DC-cut between TCXO output and LR1121 XTA
    per Semtech user manual recommendation.
    900 still needs this added in KiCad GUI.
2026-03-23 Fix 220R LCSC to C25092, add TCXO series resistor to 900
    - 220R 0201 1%: C25092 (was incorrectly C25741/100k)
    - Both 900 and Dual now have correct 220R + 10pF on TCXO→XTA path
    - Nano: RFX2401C VDD now connected to +3V3
    - All 4 schematics: 0 ERC errors
2026-03-23 Fix crystal load caps: 10pF → 18pF (C71153) on all 4 receivers
    CJ17-400001010B20 crystal has CL=10pF. With 10pF load caps and
    ~2pF stray, effective load was only 7pF (30% low). Changed to 18pF
    giving ~11pF effective load, matching the crystal spec.
    C71153 = Samsung CL03C180JA3NNNC, 18pF C0G 25V 0201.
2026-03-23 Fix Gemini crystal load caps to 18pF (C62164), matching Lite and Mono
2026-03-23 Repo cleanup: remove ERC reports, lock files, backup dirs, fix gitignore
2026-03-23 Add LCSC C430052 for 24nH XTAL_P inductor on Mono
    Mono L2 (24nH 0201) was missing LCSC field.
    Lite still needs 24nH inductor added in KiCad GUI.
    Gemini is parked — still a Mono copy, not yet dual-radio.
2026-03-23 OpenRX-Gemini: dual LR1121 schematic complete, 0 ERC errors
    - Radio 1 (U4): sub-GHz via Johanson IPD → JP1 UFL
    - Radio 2 (U9): 2.4GHz via RFX2401C (U10) → DEA (USB2) → JP3 UFL
    - Shared SPI bus (SCK/MISO/MOSI), separate NSS/IRQ/BUSY/RST per radio
    - Radio 2 control: GPIO10=NSS2, GPIO9=IRQ2, GPIO1=BUSY2, GPIO0=RST2
    - FEM driven by Radio 2 RFSW (DIO5→RXEN, DIO6→TXEN)
    - Radio 1 DIO5/DIO6 have 100k pull-downs (disconnected from FEM)
2026-03-23 Add SolderPad_1.2x2.0mm with 25% rounded corners, 2.0mm pitch standard
2026-03-23 Swap all solder pads to 1.2x2.0mm rounded (25%) across Lite, Mono, Gemini
2026-03-23 Swap 32MHz TCXO to smaller 2016 package (C22381772)
    OW2EL89 (3225, 3.2x2.5mm) → OW7EL89 (2016, 2.0x1.6mm)
    Same YXC family, same pinout, same specs. Saves 1.2x0.9mm per TCXO.
    Affects Mono (1x) and Gemini (2x).
2026-03-23 Import SKY13588-460LF SP3T RF switch (C2151906) into shared library
2026-03-23 Final topology: Mono + Gemini netlist with SKY13588 RF switch
    - SKY13588-460LF imported into shared library
    - Complete netlist for Mono (1×LR1121 + SKY13588 + Johanson IPD + DEA LPF → 1 UFL)
    - Gemini = 2× Mono RF chains + ESP32-C3 True Diversity GPIO mapping
    - GPIO maps match official ELRS Generic C3 LR1121 and True Diversity targets
    - Routing notes for RF paths included
    - Mono needs complete GPIO rewire to match ELRS target
2026-03-23 Rewrite FINAL_NETLIST.md: clean Part 1 (Mono) + Part 2 (Gemini from Mono)
2026-03-23 FINAL_NETLIST v3: SKY13588 as band combiner, RFX2401C kept for 100mW
    Based on RadioMaster XR4 teardown analysis:
    - SKY13588 serves as both sub-GHz path switch AND band combiner
    - Johanson IPD in direct-tie mode (RX/TX_LP/TX_HP joined) → SKY13588 J1
    - 2.4GHz: RFIO_HF → DEA LPF → RFX2401C → SKY13588 J2
    - SKY13588 RFC → DC block → UFL → dual-band antenna
    - RFX2401C kept for 100mW market parity
2026-03-23 FINAL_NETLIST v3.1: fix 4 issues from review
    1. SKY13588 is band-select switch, not sub-GHz path switch (direct-tie handles that)
    2. Add mandatory 0.3pF shunt on RFX2401C ANT pin to BOM and pin table
    3. Direct-tie described as deliberate 2-3dB tradeoff, not equivalent to switched
    4. radio_rfsw_ctrl must be custom, not default ELRS — use RadioMaster [15,0,12,8,8,6,0,5]
2026-03-23 Mono schematic v4: complete RF chain verified
    Verified netlist:
    - LR1121 → IPD (direct-tie, pins 6+8+9 joined) → SKY13588 J1 ✓
    - LR1121 RFIO_HF → DEA LPF → RFX2401C TXRX ✓
    - RFX2401C ANT → 0.3pF shunt → SKY13588 J2 ✓
    - SKY13588 RFC → UFL ✓
    - DIO7→V1, DIO8→V2 (band select) ✓
2026-03-24 Gemini: copy Mono schematic as base for dual-radio build
2026-03-24 Gemini: copy Mono schematic + PCB as starting point
2026-03-24 Copy Gemini PCB layout to Mono
2026-03-24 Apply JLCPCB 6-layer advanced DRC rules to Mono and Gemini
    Rules applied:
    - Min clearance: 0.09mm (3.5mil)
    - Min track width: 0.09mm (3.5mil)
    - Min via diameter: 0.25mm
    - Min via drill: 0.15mm
    - Min annular ring: 0.05mm
2026-03-24 Repo cleanup: final state for handoff
    - Clean README with architecture, BOM, CE notes, status
    - Remove dated analysis files (absorbed into FINAL_NETLIST + KICAD_WORKFLOW)
    - Remove stale OpenRX-Dual (archived), ERC reports, backups, prl files
    - Updated .gitignore for .kicad_dru, production backups
    - CERN-OHL-S v2 license confirmed
    - 3 active projects: Lite, Mono, Gemini
2026-03-24 Revise target prices in receiver specifications
    Updated target prices for Lite, Mono, and Gemini models.
2026-03-24 Consolidate active RX docs and shared project metadata
2026-04-21 initial routing for all
2026-04-24 routing
2026-04-27 final route
2026-04-28 pre-via-normalize snapshot
2026-04-28 Set via netclass + dimension defaults to 0.3/0.2mm on all 4 boards
2026-04-28 switch to 0.2mm vias
2026-04-28 Add JLC 1000-unit quote breakdown for 4-SKU panel
2026-04-28 gitignore JLC quote drops
2026-04-28 gitignore JLC per-quote BOM markdown drops
2026-04-28 appended other boarss
